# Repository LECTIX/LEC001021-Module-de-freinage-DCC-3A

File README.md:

# LEC001021-Module-de-freinage-DCC-3A
Fichiers sources pour le produit LEC001021

## Description du produit

Arrêtez et redémarrez vos convois de manière automatique et réaliste avec des arrêts et redémarrages progressifs des trains.
- **Technologie ABC**
- **Courrant maximum** de 3A.
- **Compatibilité DCC uniquement** (digital). Les décodeurs doivent être compatible avec la technologie ABC ([Cf. notice](docs/manual_fr.pdf)).

## Utiliser les fichiers sources pour fabriquer le produit

Il n'est **pas nécessaire de savoir souder ou d'être bon en électronique** pour se procurer ce produit. Grâce aux fichiers sources publiés ici, vous pouvez être en mesure de faire fabriquer ce produit par un sous traitant.

### Faire fabriquer chez un sous traitant

Il est aujourd'hui possible de faire fabriquer à moindre cout des cartes électroniques. Nous recommendons [JLCPCB](https://jlcpcb.com/) si vous voulez aller au moins cher. Si vous préférez un acteur européen, [eurocircuits](https://www.eurocircuits.com/) est un des acteurs reconnus.

1. Télécherger les sources de ce produit en cliquant sur le bouton `Code`, puis `Download ZIP`.
1. Décompresser le dossier.
1. Les fichiers pour la fabrication se trouvent dans le répertoire `hardware/prod`.
1. Se connecter sur [https://cart.jlcpcb.com/quote](https://cart.jlcpcb.com/quote)
1. Cliquer sur le bouton `Add gerber file` et sélectionner le fichier `gerbers.zip`.
1. Sélectionnez la quantité de cartes que vous souhaitez dans le champs `PCB Qty`.
1. Laisser toutes les autres options par défaut, puis cliquez sur le toggle switch en face de `PCB Assembly`, et enfin sur le bouton `confirm`.
1. Une preview de la carte électronique sans les composants doit apparaitre. Cliquez sur `NEXT`.
1. Cliquez sur le bouton `Add BOM File`, puis sélectionnez le fichier `bom.csv`
1. Cliquez sur le bouton `Add CPL File`, puis sélectionnez le fichier `pos.csv`
1. **Vérifier que tous les composants sont en stock** et bien sélectionnés, puis cliquez sur `NEXT`.
1. Une preview de la carte avec ses composants apparait. Continuer le chemin en cliquant sur `NEXT`.
1. Le prix final apparait. Sélectionnez la catégorie du produit, puis cliquez sur `SAVE TO CART`.
1. Une fois sauvegardé dans votre panier, vous pouvez valider votre commande et choisir le moyen d'acheminement. Afin de ne pas avoir à se préoccuper des frais de douane, nous vous conseillons de choisir une méthode d'expédition DDP.

Vous receverez vos cartes sous 1 à 3 semaines. 

**Nous ne sommes en aucun cas responsables des cartes qui arriveraient défectueuses ou non fonctionnelles.**

### Modifications des fichiers sources

Installez kicad 6 (ou version supérieure), et ouvrez le fichier LEC001021.kicad_pro

### Regénérer les fichiers gerber, BOM, et position (Optionnel)

Peut se faire simplement en utilisant kikit :

```
cd hardware

docker run --rm -w /kikit -v $PWD:/kikit yaqwsx/kikit kikit fab jlcpcb --assembly --no-drc --schematic LEC001021.kicad_sch --field LCSC --corrections JLCPCB_CORRECTION --nametemplate LEC001021_{} LEC001021.kicad_pcb prod/

```
## Notices
[Manuel FR](docs/manual_fr.pdf)

[Manuel EN](docs/manual_en.pdf)

[Manuel DE](docs/manual_de.pdf)
## License
Tous nos fichiers sont plubliés sous la license CERN Open Hardware Licence Version 2 - Strongly Reciprocal

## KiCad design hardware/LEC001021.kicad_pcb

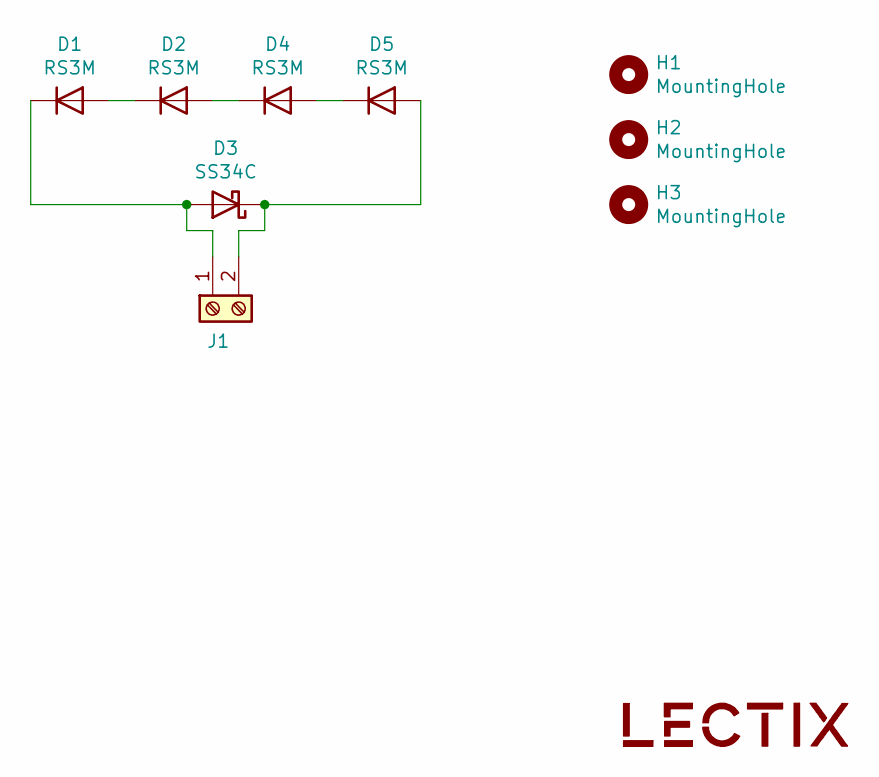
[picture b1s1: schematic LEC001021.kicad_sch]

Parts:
D1, D2, D4, D5: RS3M; D_SMC; MPN RS3M; LCSC C330389
D3: SS34C; D_SMC; MPN SS34C; LCSC C13763
H1, H2, H3: MountingHole; MountingHole_3.2mm_M3
J1: Screw_Terminal_01x02_blue; TerminalBlock_bornier-2_P5.08mm-blue; MPN DB301V-5.0-2P-BU-S; LCSC C395882
LOGO1: logo_lectix_25mm; Logo_10mm

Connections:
unnamed: D1.1 (K), D3.2 (A), J1.1
unnamed: D1.2 (A), D2.1 (K)
unnamed: D2.2 (A), D4.1 (K)
unnamed: D3.1 (K), D5.2 (A), J1.2
unnamed: D4.2 (A), D5.1 (K)

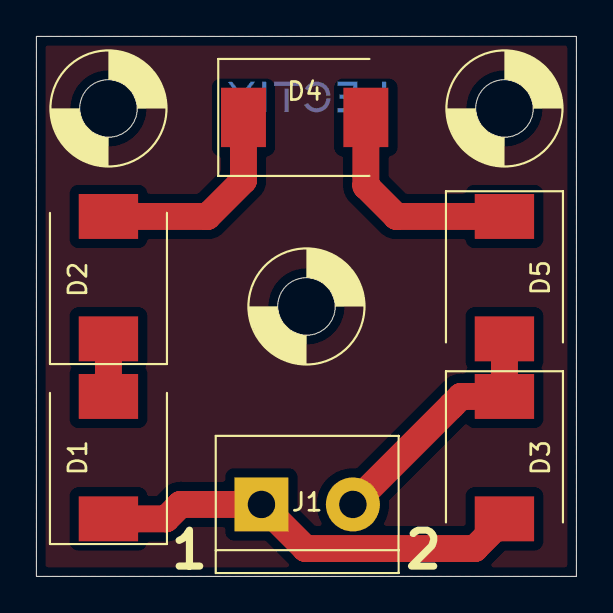
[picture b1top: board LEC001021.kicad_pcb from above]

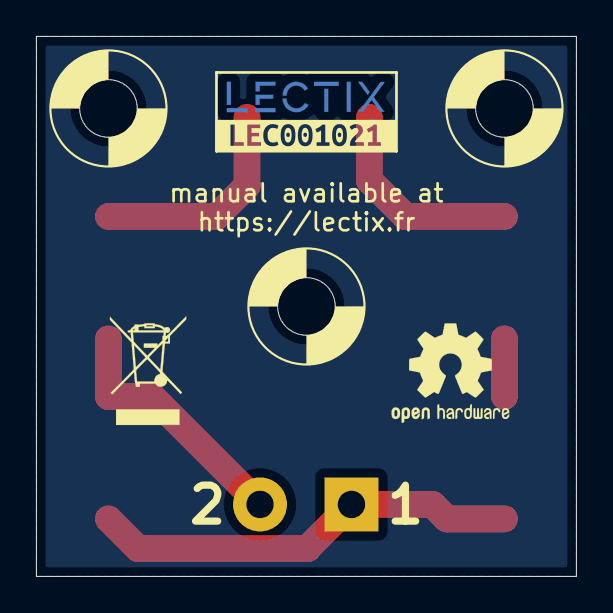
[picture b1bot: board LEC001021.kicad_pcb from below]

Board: 2 copper layers, 30.0 x 30.0 mm, 11 parts (2 on the bottom side), 5 nets.

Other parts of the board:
kibuzzard-6239BEEF: G***; kibuzzard-6239BEEF

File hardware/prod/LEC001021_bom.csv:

Comment,Designator,Footprint,LCSC
RS3M,"D1,D2,D4,D5",Diode_SMD:D_SMC,C330389
SS34C,D3,Diode_SMD:D_SMC,C13763
Screw_Terminal_01x02_blue,J1,0_connectors:TerminalBlock_bornier-2_P5.08mm-blue,C395882
logo_lectix_25mm,LOGO1,0_logos:Logo_10mm,

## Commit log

2023-03-23 docs: use CERN OHL v2 Strongly Reciprocal license
2023-03-23 docs: Add manuals
2023-03-23 docs: Add manuals link in the README file
2023-03-23 docs: Fix manuals links
2023-03-23 docs: Add spacing between manual links
2023-03-23 docs: Add product description
2023-03-23 chore: add .gitinore
2023-03-23 chore: Add product sources
2023-03-23 docs: Add reference to kicad
2023-03-23 Add .DS_Store to gitignore
2023-03-26 chore: Add prefix to prod files + put them directly into prod directory instead of in a subdirectory
2023-03-26 Add OSHW logo
2023-03-26 Add pdf schematic file
2023-03-26 Add tuto video
